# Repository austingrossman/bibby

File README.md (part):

# bibby — Brew In A Bag Temperature Ramp Controller

`bibby` is a temperature and power controller for electric brew-in-a-bag (BIAB)
brewing, running on a Raspberry Pi 5. It reads kettle temperature from a PT100
RTD, drives two mains heating elements through solid-state relays (SSRs), and
presents a touch UI for setting and tracking the brew temperature. Power is
delivered as a duty cycle synchronized to the AC mains zero crossing, and the
whole system is built so that any fault, crash, or hang leaves the heaters
**off**.

This README is meant to let someone unfamiliar with the project understand it,
reproduce the hardware, build the software, and calibrate it for their own
kettle. It moves from the big picture down to the details: architecture, then
hardware, then software, then build/bring-up, then calibration.

This project is for fun. I am doing it to improve my home brewing set up. I hope
that someone sees inspiration in this project and does something similar. I am
doing this with a couple specific goals in mind:
- Learn to use AI for coding purposes.
- I recently purchased a Mac mini. I will only use a Mac for this project and it
  forces me to learn how to use it.
- I've recently acquired a 3D printer. This project has one 3D printed part, so
  I should learn how to use it.

---

## Table of contents

1. [System overview](#1-system-overview)
2. [Software architecture](#2-software-architecture)
3. [Safety design](#3-safety-design)
4. [Hardware](#4-hardware)
5. [Raspberry Pi bring-up and installation](#5-raspberry-pi-bring-up-and-installation)
6. [Building bibby](#6-building-bibby)
7. [Configuration](#7-configuration)
8. [Running](#8-running)
   - [Web interface — screen mirror + log browser](#web-interface)
9. [Calibration methodology](#9-calibration-methodology)
10. [Data logging](#10-data-logging)
11. [Repository layout](#11-repository-layout)
12. [License](#12-license)

---

## 1. System overview

The controller is a **single process** with three threads sharing one in-memory
state block of C11 atomics (the optional web interface adds a few more, none of
them on the control path — §2.9):

```
  +----------------------------------------------------------------+
  |                    bibby (one process)                          |
  |                                                                |
  |  main/UI thread          sampler thread         SSR thread     |
  |  ---------------         ------------------     -------------  |
  |  LVGL touch UI on        60 Hz, DRDY-paced:     SCHED_FIFO,    |
  |  /dev/fb0 (rotated)      - MAX31865 read        ZC-paced:      |
  |  - kettle readout        - temp filter          - zero-cross   |
  |  - charts, slider        - PID (watts)            capture      |
  |  - fault band            - power split          - sigma-delta  |
  |          |               - CSV logging            SSR firing   |
  |          |               - batch-size estimator - watchdogs    |
  |          v                     |                     |         |
  |  +------------------ BibbyState (C11 atomics) -------+         |
  |            duties, temps, modes, faults, history               |
  +----------------------------------------------------------------+
        | SPI0 + DRDY (GPIO16)      | GPIO20 ZC     | GPIO21/26
        v                           |               v
  +-------------+            +-------------+   +-----------+
  |  MAX31865   |            | zero-cross  |   |   SSR1    |
  |  + PT100    |            | detector    |   |   SSR2    |
  +-------------+            +-------------+   +-----------+
        ^                          ^                |
        | RTD                      | AC mains       | switched mains
     kettle probe                  line sense       to heating elements
```

- The **SSR thread** owns the relays. It runs at real-time priority
  (`SCHED_FIFO`) so a GUI stall can never delay the zero-cross response or the
  watchdogs.
- The **sampler thread** owns the sensor and the control law. It publishes
  per-element duty commands into the shared state; it never touches the relays.
- The **UI thread** is a pure view/controller: it renders the state and writes
  user intent (setpoint, mode, manual watts). Nothing in it is on the control
  or safety path.
- Optionally, the **web interface** (§2.9) adds an accept thread, a
  framebuffer-capture thread and a short-lived thread per HTTP connection. They
  run at normal priority, hold no control state of their own, and reach the
  controller only by injecting pointer events into the UI — so everything above
  is unchanged whether it is running or not.

### Why a duty cycle synchronized to zero crossing?

The heating elements are resistive loads switched by zero-cross SSRs. Switching
only at the AC zero crossing eliminates the inrush/EMI of phase-angle control.
Power is modulated by choosing *which* mains half-cycles to pass — a duty cycle
in `[0, 1]`. A sigma-delta modulator (§2.3) spreads the fired cycles out evenly
so the average power tracks the command with minimal low-frequency flicker.

### Why watts, not duty?

The control law works in **watts**: the PID outputs a total power demand, and a
splitter turns watts into per-element duties using the configured element
ratings. This makes the tuned gains independent of which elements are fitted —
swap elements, update `bibby.ini`, and the loop still commands the same power
per degree of error. It also enables the equal-flux split and anti-scorch cap
(§2.4), which need to know real watts per cm².

---

## 2. Software architecture

### 2.1 Shared state — `src/state.{h,c}`

`BibbyState` is a single struct of C11 atomics shared by the three threads —
no locks on the hot paths. Key fields:

| Field | Writer | Purpose |
|---|---|---|
| `duty1`, `duty2` | sampler | per-element duty commands in `[0,1]` |
| `p_demand_w` | sampler | commanded power — also the delivered average power (§2.3) |
| `temp_raw_c`, `temp_filt_c`, `temp_valid` | sampler | latest sensor sample and validity |
| `setpoint_c`, `manual_mode`, `manual_power_w`, `grain_in` | UI | user intent |
| `simulate_zc` | main, at startup | bench zero-cross simulation (`mains.simulate_zc` / `--sim-zc`); never changes while running |
| `output1`, `output2`, `zc_count`, `watchdog_alarm` | SSR thread | fired state, ZC counter, ZC watchdog |
| `control_heartbeat` | sampler | bumped every loop pass; the SSR thread's staleness watchdog watches it |
| `rtd_fault`, `rtd_unresponsive`, `fault_forced_manual` | sampler | sensor-fault state |
| `m_est_l`, `adaptive_scale` | sampler | batch-size estimate (litres) and gain scale |
| `running` | main | global shutdown flag |

A mutex-guarded ring buffer of `HistPoint`s (one per 0.5 s) feeds the UI
charts; it is the only locked structure, and only the UI and the sampler's
0.5 s slow tick touch it.

### 2.2 Sampler thread — `src/sampler_thread.c`

Paced by the MAX31865 DRDY edge (one conversion per mains cycle, so ~60 Hz):

1. **Wait** for a DRDY falling edge (500 ms timeout so a dead sensor cannot
   stall the loop — the read also checks the DRDY level directly, so a missed
   edge still yields the conversion).
2. **Read** the sensor (§2.5); fresh samples go through the temperature filter
   (§2.6) and into the shared state.
3. **Mode interlock:** any RTD fault, unresponsive sensor, or invalid
   temperature forces **manual mode at zero watts** — automatic control can
   never command power on bad data.
4. **Control law** (§2.4): manual watts pass straight through; in auto, the
   watts-based PID runs once per fresh sample.
5. **Power split** (§2.4) turns the demand into `duty1`/`duty2`.
6. **Slow tick (0.5 s):** publish the batch-size estimate (§2.7) and push a
   chart history point.
7. **CSV logging** (§10): one row per fresh sample (or per 0.5 s during an
   outage, so faults stay on disk).

### 2.3 SSR thread — `src/ssr_thread.c`, `src/sigma_delta.h`

Runs at `SCHED_FIFO` (real-time) priority, pinned to the AC zero crossing:

1. **Zero-cross capture.** Wait for a rising edge on GPIO20 (libgpiod v2 edge
   events) with a mains-derived timeout: half-period + 0.7 ms guard — 9.0 ms at
   60 Hz, 10.7 ms at 50 Hz.
2. **Sigma-delta modulation.** Each zero crossing, add each element's duty
   fraction to a per-channel accumulator; fire that SSR for the half-cycle when
   the accumulator reaches 1.0 and subtract 1.0. The accumulator is capped at
   2.0 to bound catch-up after forced-off stretches. This is a first-order
   delta-sigma DAC clocked by the mains: the average fired fraction equals the
   commanded duty with the switching energy pushed to high frequency.
3. **Zero-cross watchdog.** No edge within the timeout → both SSRs forced off,
   `watchdog_alarm` set. A lost mains-sense signal must not leave a relay
   latched on. `simulate_zc` substitutes the timeout tick for the edge so the
   modulator can be exercised with no mains connected. It is set once at
   startup from `mains.simulate_zc` (or `--sim-zc`) and there is deliberately
   **no control for it on the panel**: while it is on this watchdog can never
   trip, which is a commissioning decision, not something a stray tap during a
   brew should be able to do. Startup logs a warning line whenever it is on.
4. **Control-staleness watchdog.** The sampler bumps `control_heartbeat` every
   pass; if it stops advancing for ~2 s worth of zero crossings
   (`2 × mains_Hz`), duties are forced to zero — a wedged control loop must not
   leave the heaters running. (`BIBBY_TEST_WEDGE=<sec>` wedges the sampler once,
   5 s in, to demonstrate exactly this on the bench.)

### 2.4 Control law — `src/control.c`, `src/power_split.c`

**PID (watts).** `p = kp·e`, integrator accumulates raw per-sample error
(`ki` is W/°C per sample), derivative is a raw per-sample delta. Output is
`clamp(ff + p + i + d, 0, max_power)` in watts. Anti-windup is **conditional
integration**: the integrator holds whenever the non-integral output is already
against a rail and the error would push further into it; a backstop clamps the
integral term to full output authority (`max_power / ki`).

**Integral clamp** (`pid.i_clamp_w`, watts; 0 = off). On top of that, the
integral *term* is bounded to ±`i_clamp_w` — the accumulator itself is held to
`i_clamp_w / ki`, every step, whether or not the integrator was allowed to
move. It is a statement of how much authority the integrator may ever have:
with the feedforward carrying the holding power, all the integrator has to
trim is model error, so it never needs kilowatts. The shipped value is 500 W,
about 5 % of the installed 10.5 kW — enough to absorb a wrong ambient or a
drifting `k_loss`, far too little to run away with the kettle. The tighter of
this and the `max_power / ki` backstop wins, and it applies to both gain sets.

**Integral separation** (`pid.i_band_c`, °C; 0 = off). The integrator only
accumulates while `|error| ≤ i_band_c`; outside the band it holds its value,
neither growing nor resetting. Anti-windup alone is not enough on this plant:
the kettle is an integrator, so a PI with an accurate feedforward must finish
a setpoint change with its integrator back near zero, which means every
degree-second of error it soaked up during the approach is paid back as
overshoot after the crossing. In the 2026-09-07 ramp test that accounted for
the whole 0.73 °C overshoot on a 10 °C step: the output was railed (and the
integrator held) only for the first 4 °C, then the integrator wound up for
250 s across the unsaturated approach and was still commanding 1.7 kW over
the holding power when the temperature first touched setpoint. With the
feedforward carrying the holding power the integrator has only model error to
trim, and there is nothing useful for it to learn while the temperature is
still degrees away, so the band confines it to the last half degree. The
band applies to both gain sets.

**Holding feedforward.** `ff = (setpoint − ambient_c) / process_gain_c` watts,
clamped to `[0, max_power]` — the steady-state power needed to hold the
setpoint, supplied directly so the integrator only trims model error (§9.6).
Zero gain disables it.

**Grain-in gain set.** The "Grain In" toggle swaps in an alternate gain set
(`grain.kp/ki/kd`) and optionally caps power (`grain.max_power_w`) — the plant
changes when grain is added, and scorch risk rises. Zero grain gains mean
"same as main gains disabled" (auto commands no power in grain mode until they
are set).

**Adaptive gain scaling** (config-gated, off by default). The batch-size
estimate in litres (§2.7) divided by `adaptive.m_ref_l` scales `kp`/`kd`
within `[scale_min, scale_max]` — a half-size batch gets half the gain without
retuning.

**Equal-flux power split.** Demand is split so both elements run at the same
surface power density (W/cm²): proportional to area, with saturation overflow
pushed to the other element and everything clamped to the element ratings.
With different elements (e.g. 5000 W/820 cm² + 5500 W/473 cm²) the duties are
deliberately unequal — same flux, different power. `power.max_flux_w_cm2`
optionally caps total demand at `flux × total_area` (anti-scorch; 0 disables).

### 2.5 MAX31865 RTD sensor — `src/max31865.c`

- PT100, **3-wire**, 400 Ω nominal reference resistor, on `/dev/spidev0.0` at
  1 MHz, `SPI_MODE_1`.
- **Init sequence:** set 3-wire + clear faults + mains filter notch → enable
  VBIAS (10 ms settle) → enable auto-conversion (20 ms) → discard the first 10
  conversions using DRDY polling (they settle after VBIAS/auto enable).
- **Mains filter:** config-register bit 0 selects the noise-rejection notch
  (set = 50 Hz, clear = 60 Hz). It is set from `mains.frequency_hz` (§7) in the
  first config word — before auto-conversion, as the datasheet requires.
- **`max31865_read()` is non-blocking:** it checks the DRDY level (GPIO16,
  active-low); not ready → previous value with `fresh=false`. Otherwise it
  burst-reads RTD + fault registers in one SPI transaction, converts via
  Callendar–Van Dusen, and applies the per-unit `Rref`/gain/offset calibration
  (§9.1–9.2).
- **Fault handling:** the RTD-LSB fault bit and Fault Status register are
  checked every read. A faulted conversion is rejected (the stale value is held
  so the filter is not poisoned) and the latch cleared so the status reflects
  the next conversion. `max31865_fault_text()` decodes the register for the UI
  fault band.

The MAX31865 datasheet is included at [`docs/MAX31865.pdf`](docs/MAX31865.pdf).

### 2.6 Temperature filter — `src/temp_filter.c`

Cascaded boxcar (moving-average) stages — order and window from `bibby.ini`
(default 2 × 40 samples ≈ a second-order CIC with triangular weighting, ~0.65 s
group delay at 60 Hz). The first sample primes every stage so the output starts
at the true temperature instead of ramping from zero.

### 2.7 Batch-size estimator — `src/mass_estimator.c`

During any stretch of roughly constant commanded power (taken as 0 W while the
ZC watchdog holds the SSRs off) where the temperature rises ≥ 1 °C, the kettle behaves as an integrator: `dT/dt = P/(m·c)`. A
least-squares slope over the stretch gives the thermal mass `P/slope` in J/°C,
which is reported as the equivalent litres of water, `m = (P/slope)/4186`, so
the number on the status line (`m 53.2 L`) and in the log (`m_est_l`) is a
batch size a brewer can sanity-check against what they poured in. It reads a
little high because the kettle, elements and hoses count as water, and it
reads `1/s` high when the elements put out a fraction `s` of their rated watts
(the shipped setup reads 53 L for 45 L poured; §9.4). It is always computed
and logged; feeding it back into the gains is the separate, config-gated
adaptive scaling of §2.4.

### 2.8 UI — `src/ui/`

LVGL 9.3 rendering directly to the framebuffer:

- **Display:** `lv_linux_fbdev` on `/dev/fb0`; the physical panel is portrait,
  mounted sideways, so the UI renders 1280×720 and LVGL software-rotates 90°
  into the 720×1280 framebuffer (`ui.rotation`). Touch comes from the first
  evdev device advertising absolute multitouch (`ui.touch_device = auto`).
- **Layout:** two large square toggles (Grain In, Manual Control) and the
  ±10/±1/±0.1 setpoint steppers on top; temperature chart (setpoint, filtered,
  raw, grain and mode-change markers) and power/PID-term chart below, each
  between a row of tappable legend chips above and a time scale below; a wide
  vertical power slider (manual watts in manual, live demand readout in auto);
  kettle graphic whose element glow follows the commanded duties and whose
  contents carry the batch-size estimate in litres and gallons, with the
  per-element duties and the adaptive gain scale under it; fault band (decoded
  RTD faults, watchdog, forced-manual notice).
- **Time scale:** both charts are right-aligned to *now* and span
  `ui.chart_window_min`, so the scale is fixed at startup and drawn once —
  six marks running `-5m … -1m … now` for the default 5-minute window, landing
  exactly on the chart's vertical grid lines (sub-minute marks read `-0:30`).
- **No dead space.** The two panes stretch from just under the toggles to the
  bottom edge. The fault band has no reserved strip: it is hidden nearly
  always, so it floats over the lower third of the power chart when it
  appears, which costs nothing — the loop is at zero watts by then.
- **Sized for fingers, not a mouse.** Every target is a touch target: the two
  toggles are 180×160, the steppers 120×75, the legend chips 46 px tall, and
  the power slider is 104 px wide — it is the only continuous control on the
  screen, so it gets a thumb's worth of track. The one thing the panel
  deliberately cannot do is arm zero-cross simulation (§2.3).
- LVGL is pinned to **v9.3.0**: v9.4 breaks the fbdev software-rotation path
  and hangs in `lv_deinit` on shutdown.
- **Memory (`src/ui/lv_conf.h`):** LVGL's built-in allocator is a fixed pool
  sized for microcontrollers — 64 KB by default, and this screen sits at ~36 KB
  of it with peaks near 42 KB, so a large redraw could exhaust the remainder and
  assert inside `lv_draw_add_task` ("Out of memory"). bibby therefore sets
  `LV_USE_STDLIB_MALLOC = LV_STDLIB_CLIB`: LVGL allocates from the system heap
  and there is no ceiling to tune.
- **Assertions:** LVGL's default `LV_ASSERT_HANDLER` is `while(1);`, which would
  wedge the UI thread at 100 % CPU — panel frozen, SIGTERM ignored, control
  threads still driving the elements. bibby sets it to `abort()` instead: the
  process dies, the kernel drops the GPIO requests, the SoC pull-downs hold the
  SSR inputs low, and `bibby.service` restarts it (§5.3).
- The kernel console shares `/dev/fb0` and will draw its blinking cursor over
  the UI; the systemd unit unbinds it (§5.3).

`bibby --ui-test` shows a bring-up screen instead: border, corner labels, and a
crosshair that follows the finger — verifies rotation and touch mapping before
trusting the real UI.

### 2.9 Web interface — `src/web/`

Optional, off by default, and configured entirely from `[web]` in `bibby.ini`
(§7). When enabled it adds an HTTP server on the LAN with two screens: a live
mirror of the touchscreen that can be tapped from a phone or laptop, and a
browser for the CSV run logs. Operator's guide in §8; safety in §3.

```
             browser                       bibby process
   ┌──────────────────────────┐   ┌────────────────────────────────────┐
   │  Screen tab              │   │  accept thread ─┬─ conn thread ─┐  │
   │    long-poll   ─────┼───┼──> /api/screen.png              │  │
   │   pointer events    ─────┼───┼──> /api/input                   │  │
   │                          │   │                                 v  │
   │  Logs tab                │   │        capture thread     pointer  │
   │   file list, charts ─────┼───┼──> /api/logs /api/log     queue    │
   │   CSV download      ─────┼───┼──> /api/log/download        │      │
   └──────────────────────────┘   │             │               │      │
                                  │        mmap /dev/fb0        │      │
                                  │             │          UI thread   │
                                  │             └──────────> LVGL indev│
                                  └────────────────────────────────────┘
```

- **Screen mirror.** The capture thread `mmap`s `/dev/fb0` read-only and
  compares it against the previous frame; only a genuine pixel change bumps the
  frame sequence. It captures at most `web.screen_fps` times a second, and only
  while a browser is actually asking — an unwatched panel costs nothing.
  Requests **long-poll**: the server holds `/api/screen.png?seq=N` until the
  screen differs from the client's frame `N` (or 10 s pass, answering `204`), so
  a static screen uses no bandwidth and a touch appears within one frame.
  Frames are encoded as PNG (zlib, "Up" filter) — about 50 KB for a full
  1280×720 frame, and `?scale=2` halves each dimension for slow links.
- **Un-rotation.** The framebuffer is the *physical* portrait panel, sideways;
  the mirror applies `ui.rotation` so the browser shows what the operator at the
  kettle sees. The forward map is the same one LVGL uses on pointer input, so
  "display space" here is exactly LVGL's logical screen.
- **Pointer injection.** Taps post to `/api/input` in display coordinates. The
  server maps them back to panel coordinates and pushes them onto a small queue;
  a **second LVGL pointer indev**, created on the UI thread, drains that queue
  and reports the samples exactly as the evdev touchscreen does — so LVGL
  applies the same rotation to a remote tap as to a finger, and it lands on the
  pixel it looks like it lands on. LVGL is single-threaded and this queue is the
  entire boundary: no web thread ever makes an `lv_*` call. A press with no
  follow-up is auto-released after 2 s, so a browser that vanishes mid-drag
  cannot leave a widget held down.
- **Log browser.** `/api/logs` walks the CSV tree; `/api/log` streams one file
  through a bounded-memory decimator (rows accumulate into buckets; when the
  bucket array fills, adjacent buckets merge pairwise and the rows-per-bucket
  doubles) and returns a whole-file average of at most ~1400 points per series.
  A 75 MB, 459 k-row tuning log becomes 136 KB of JSON in about a second.
  `/api/log/download` serves the raw CSV, including the run in progress.
- **Path safety.** Every client-supplied path is `realpath()`d and required to
  resolve inside `~/bibby/logs` and to be a regular `.csv` file, so the server
  cannot be talked into serving anything else.
- **Authentication.** HTTP Basic against `web.user` / `web.password`, compared
  length-independently so a wrong password cannot be narrowed down by timing.
  The server **refuses to start with an empty password**. Failures are logged
  and answered after a 300 ms delay.
- **Cost.** Nothing at all when no browser is watching — the capture thread
  sleeps on a condition variable. With one browser on the Screen tab, measured
  on a Pi 5 at 1280×720 (percentages are of **one** core, of four; bibby idles
  at ~1.4 %):

  | | per frame | 2 fps | 5 fps |
  |---|---|---|---|
  | full resolution | ~19 ms, ~48 KB | ~5 % | ~11 % |
  | `scale=2` | ~8 ms, ~25 KB | ~3 % | ~6 % |

  The cost is linear in `web.screen_fps`, and the dominant term is the
  **un-rotate/pixel conversion (~8 ms), not the PNG compression (~11 ms
  including the filter)** — rotating means walking the framebuffer down a
  column, which defeats the cache. Two things keep it in hand: the conversion
  precomputes a per-pixel and per-row byte step instead of transforming each
  pixel's coordinates (worth ~10×), and the build is optimized (§6 — an
  unoptimized build costs ~67 ms per frame instead of 19). The web threads run
  at normal priority and are not on the control path; the SSR thread's
  `SCHED_FIFO` and the staleness watchdog are unaffected either way.
- The page is a single self-contained HTML file (`src/web/www/index.html`, no
  external assets or CDN) compiled into the binary at build time, so an
  installed `bibby` has no companion asset directory to lose.

---

## 3. Safety design

This system switches mains voltage into multi-kilowatt heating elements, so the
**default state is always off**. The design requirements and how they are met:

| Requirement | Mechanism |
|---|---|
| Heaters off at startup | SSR GPIO lines are requested with output value low before any thread runs |
| Heaters off on exit/crash | the kernel releases the GPIO lines when the process dies — for any reason — and the SoC pull-downs hold the SSR inputs low; SIGINT/SIGTERM additionally shut down in order |
| Only one instance | `flock` single-instance guard (`src/single_instance.h`); the kernel drops the lock on any exit |
| Heaters off if mains-sense (ZC) is lost | mains-derived zero-cross watchdog (~9 ms at 60 Hz) forces SSRs off, raises `watchdog_alarm`. The one thing that defeats it is bench mode (`mains.simulate_zc`, §2.3), which is why it lives in the config file and has no control on the panel |
| Heaters off if the control loop wedges | control-staleness watchdog: sampler heartbeat stalled for ~2 s of ZCs → duties forced to zero |
| GUI stalls cannot delay safety logic | the SSR thread runs `SCHED_FIFO`; the UI is not on the control path |
| No power commanded on unreliable temperature | RTD fault / unresponsive sensor forces manual mode at zero watts; auto is unreachable until the sensor is healthy |
| Power commands always bounded | demand clamped to the configured element ratings (and the optional flux cap) before splitting; duties clamped to `[0,1]` |
| The integrator cannot run away | conditional-integration anti-windup, plus a hard ± bound on the integral term (`pid.i_clamp_w`, 500 W as shipped) and the `max_power / ki` backstop (§2.4) |
| A vanished web client cannot hold a control down | an injected press with no follow-up sample is released after 2 s |
| Controller returns after a crash | `Restart=always` in the systemd unit (§5.3); SSRs are safe during the gap per the kernel-release mechanism above |
| Remote control cannot bypass an interlock | the web interface owns no control logic: it injects pointer events into the same LVGL widgets a finger drives (§2.9), so mode interlocks, clamps and watchdogs apply identically |
| Remote control is off unless deliberately enabled | `[web]` is disabled by default and the server refuses to start without a password; `web.allow_control = false` serves a read-only mirror |

---

## 4. Hardware

### 4.1 Major components

| Item | Notes |
|---|---|
| Raspberry Pi 5 | GPIO chip is `/dev/gpiochip4` on Pi 5 |
| Touchscreen display | 720×1280 DSI panel (Goodix touch), mounted sideways; UI software-rotates 90° |
| PT100 RTD probe | 3-wire, immersed in the kettle |
| 2 × zero-cross SSR | One per heating element; switched by GPIO21 / GPIO26 |
| 2 × resistive heating element | Mains-powered, BIAB kettle (this build: 5000 W and 5500 W) |
| Custom Pi HAT PCB | Sensor front-end + zero-cross detector (§4.2) |

> **TODO (fill in your build):** exact display model, SSR part numbers and
> current rating, fusing/contactor, and mains connector. These are
> deployment-specific and not captured in the repo.

### 4.2 Raspberry Pi HAT PCB — `pi_hat/bibby_pi_hat/`

A KiCad 7+ project (`.kicad_sch`, `.kicad_pcb`, `.kicad_pro`). Open it in KiCad
to view/edit the schematic and board, or to regenerate gerbers
(`pi_hat/bibby_pi_hat/gerbers/`). The HAT carries two functional blocks:

**RTD front-end (U1 — MAX31865):**
- `R1` = 400 Ω 0.1 % — RTD reference resistor (`Rref`). Precision and tempco here
  set the measurement accuracy; this is one of the two per-unit calibration
  anchors (§9.1).
- `C1`, `C3` = 0.1 µF — decoupling / RC filtering.
- SSOP-20 package; SPI to the Pi plus the DRDY data-ready line.

**AC zero-cross detector (U2 — H11AA1 AC-input optocoupler):**
- The H11AA1 has an anti-parallel LED input, so it conducts on both mains
  half-cycles and its phototransistor output pulses around each zero crossing.
- `R3`–`R6` = 43 kΩ, `R2` = 20 kΩ, `R7` = 1 MΩ (! DNI !) — line current-limiting
  and pull/bias network for the optocoupler. The pulse train feeds GPIO20.
- Solder jumpers `JP1`/`JP2`/`JP3` select options on the board.

**Connectors:**
- `J1` — 2×20 stacking header to the Pi GPIO.
- `J2` — Phoenix 1×10 5.08 mm terminal block (field wiring: RTD, mains sense,
  SSR drive).

> The complete, authoritative bill of materials and net list is the KiCad
> schematic itself. The values above are transcribed from it for orientation.

### 4.3 Pin assignments (40-pin header)

| Pin | GPIO | Signal | Direction | Used by |
|---|---|---|---|---|
| 1 | — | 3.3 V | Power | MAX31865 VIN |
| 6 | — | GND | Power | MAX31865 GND |
| 19 | GPIO10 | SPI0 MOSI | Out | MAX31865 SDI |
| 21 | GPIO9 | SPI0 MISO | In | MAX31865 SDO |
| 23 | GPIO11 | SPI0 SCLK | Out | MAX31865 CLK |
| 24 | GPIO8 | SPI0 CE0 | Out | MAX31865 CS |
| 36 | GPIO16 | DRDY | In | MAX31865 DRDY (sampler thread) |
| 37 | GPIO26 | SSR2 | Out | SSR thread |
| 38 | GPIO20 | Zero Cross | In | SSR thread |
| 40 | GPIO21 | SSR1 | Out | SSR thread |

### 4.4 Electrical / wiring overview

```
   MAINS L ---+----------------------------+--------------------+
              |                            |                    |
              |                       [SSR1 load]          [SSR2 load]
              |                            |                    |
        [ZC detector U2]             [Element 1]          [Element 2]
              |  (opto, isolated)          |                    |
              v                       [SSR1 line]          [SSR2 line]
        GPIO20 (ZC in)                     ^                    ^
                                           |                    |
   Pi 3.3V/GPIO control side:        GPIO21 (SSR1)        GPIO26 (SSR2)
                                      drive (3.3V logic into SSR input)

   PT100 RTD --3 wires--> MAX31865 (U1) --SPI0 + DRDY--> Pi
```

- The H11AA1 provides **galvanic isolation** between the mains line-sense and
  the Pi logic.
- The SSRs are driven by 3.3 V GPIO on their input side; their output side
  switches mains into the elements.
- The RTD is a low-voltage measurement isolated from the mains by the kettle
  and the sensor front-end.

> **WARNING:** mains wiring, fusing, grounding/earth bonding, and enclosure
> safety are the integrator's responsibility. Use appropriately rated SSRs and
> heat-sinking, a proper earth connection to the kettle, and a
> contactor/fuse/breaker sized to the elements.

### 4.5 Enclosure

> **TODO (fill in your build):** enclosure material and dimensions, panel cutout
> for the display, ventilation/heat-sinking for the SSRs, and how the Pi + HAT +
> SSRs are mounted. Add photos and mechanical drawings here.

---

## 5. Raspberry Pi bring-up and installation

Tested target: **Raspberry Pi 5**, 64-bit Raspberry Pi OS.

### 5.1 OS and interfaces

1. Flash Raspberry Pi OS (64-bit) and boot the Pi. Install a beefy SD card (or
   other storage) for logging. Find a way to remote-login to the Pi.
2. Enable SPI:
   ```
   sudo raspi-config   # Interface Options -> SPI -> Enable
   ```
   Confirm `/dev/spidev0.0` exists after reboot.
3. The DSI touch display is auto-detected (`display_auto_detect=1` in
   `/boot/firmware/config.txt`). The touch controller registers as a Goodix
   evdev device; bibby finds it automatically.
4. The Pi 5 exposes GPIO via `/dev/gpiochip4`; the code opens it directly. The
   user running bibby needs the `gpio`, `spi`, `video`, and `input` groups (or
   run via the systemd unit, §5.3).

### 5.2 Build dependencies

```
sudo apt update
sudo apt install -y build-essential cmake git libgpiod-dev zlib1g-dev
```

- **libgpiod v2** is required (the code uses the v2 edge-event API). Confirm
  with `gpiodetect` / `pkg-config --modversion libgpiod`.
- **LVGL** is fetched and built from source by CMake (FetchContent) — nothing
  to install. It renders straight to the framebuffer; no X, Wayland, or GL
  stack is needed.
- The analysis tools (§9.4) additionally want
  `pip3 install numpy scipy matplotlib pandas` on whatever machine runs them.

### 5.3 Autostart at boot (systemd)

[`deploy/bibby.service`](deploy/bibby.service) is the reference unit. Besides
starting bibby it handles three things the app cannot do for itself:

- **Unbinds the kernel console from the framebuffer** (`vtcon1`) before start —
  otherwise the console's blinking cursor (and any kernel message) draws over
  the UI — and rebinds it on stop.
- **`LimitMEMLOCK=64M`** so `mlockall(MCL_CURRENT)` succeeds (the default 8 MB
  is too small once LVGL is linked in).
- **`AmbientCapabilities=CAP_SYS_NICE`** so the SSR thread gets its `SCHED_FIFO`
  real-time priority without running the whole process as root.

Install:

```
sudo cp deploy/bibby.service /etc/systemd/system/
sudo systemctl daemon-reload
sudo systemctl enable --now bibby
```

Check status and logs with `systemctl status bibby` / `journalctl -u bibby -f`.
Adjust `User=` and the paths in the unit for your username/checkout. The unit
uses `Restart=always`: the controller comes back if it ever dies, and the SSRs
are safe during the gap (§3).

---

## 6. Building bibby

```
git clone <repo-url> bibby
cd bibby
cmake -S . -B build -DCMAKE_BUILD_TYPE=Release
cmake --build build -j
```

If you omit `CMAKE_BUILD_TYPE`, CMake would normally configure with **no `-O`
flag at all**; `CMakeLists.txt` therefore defaults it to `RelWithDebInfo`
(`-O2 -g`) when it is unset. This matters more than it sounds: an unoptimized
build runs LVGL's renderer and the web mirror's pixel conversion roughly four
times slower (§2.9). Check an existing build tree with

```
grep C_FLAGS build/CMakeFiles/bibby.dir/flags.make
```

and re-run `cmake -S . -B build -DCMAKE_BUILD_TYPE=RelWithDebInfo` if it shows
no `-O2` — a build directory keeps whatever type it was first configured with.

The first configure fetches LVGL (pinned to v9.3.0 — see §2.8) from GitHub.
Two binaries result:

- `build/bibby` — the controller (links `lvgl`, `gpiod`, `z`, `m`, `pthread`,
  `rt`; `z` is only used by the web screen mirror, §2.9)
- `build/tests` — unit tests for the pure modules (no hardware needed):

```
./build/tests
```

`build/` and `logs/` are gitignored. There is no install step yet; run from the
build tree (the systemd unit does the same). The config file is found relative
to the executable (§7), so a copied-out binary works if `bibby.ini` sits next
to it.

---

## 7. Configuration

Runtime parameters that depend on the install (mains region, heating elements,
control gains, calibration) live in **`bibby.ini`**, **not** in the source.
There is no reason to edit a constant in code and rebuild to adapt a new brew
setup.

**Lookup order:** `-c <path>` argument → `$BIBBY_CONFIG` environment variable →
`bibby.ini` next to the executable → `bibby.ini` in the current directory.
A missing file or unknown key falls back to a built-in safe default (60 Hz,
zero gains), so the system still comes up. Comments (`#` or `;`, inline
allowed) and blank lines are ignored.

All keys, with their defaults:

| Key | Default | Effect |
|---|---|---|
| `mains.frequency_hz` | 60 | ZC watchdog timeout (half-period + 0.7 ms), staleness cutoff (2×Hz ZCs ≈ 2 s), MAX31865 notch (50/60 Hz) |
| `mains.simulate_zc` | false | **bench only:** treat ZC-watchdog timeouts as zero crossings, so the whole loop runs with no AC connected (§2.3). The mains-loss watchdog cannot trip while it is on, so it is a config switch with no panel control; `--sim-zc` forces it on for one run |
| `element1.watts` / `element2.watts` | 2500 / 2500 | element ratings; their sum is the maximum power demand |
| `element1.area_cm2` / `element2.area_cm2` | 150 / 150 | wetted areas driving the equal-flux split |
| `power.max_flux_w_cm2` | 0 (off) | anti-scorch cap: total demand ≤ flux × total area |
| `pid.kp` / `ki` / `kd` | 0 | watts-based gains (§9.5); zero = auto commands no power |
| `pid.i_band_c` | 0 (off) | integral-separation band, °C: the integrator only accumulates within it (§2.4); both gain sets |
| `pid.i_clamp_w` | 0 (off) | ± bound on the integral term, watts (§2.4); the tighter of this and the `max_power / ki` backstop applies; both gain sets |
| `grain.kp` / `ki` / `kd` | 0 | alternate gain set while "Grain In" is on |
| `grain.max_power_w` | 0 (off) | power cap while grain is in |
| `feedforward.process_gain_c` | 0 (off) | identified K [°C/W]; holding feedforward `(setpoint−ambient)/K` watts |
| `feedforward.ambient_c` | 20 | feedforward reference temperature |
| `sensor.ref_resistor_ohms` | 400 | MAX31865 Rref, ice-point trimmed (§9.1) |
| `sensor.temp_cal_gain` / `temp_cal_offset` | 1.0 / 0.0 | two-point span trim, `T_true = g·T + b` (§9.2) |
| `filter.order` / `filter.window` | 2 / 40 | boxcar cascade stages and window length (§2.6) |
| `logging.rate` | high | `high` = row per sample (60 Hz); `low` = row per `low_period_s` |
| `logging.low_period_s` | 2.0 | row period in low-rate mode |
| `ui.chart_window_min` | 5 | chart time window, minutes (1–30) |
| `ui.rotation` | 90 | UI rotation onto the panel: 0/90/180/270 |
| `ui.fb_device` / `ui.touch_device` | auto | `auto` = `/dev/fb0` / first multitouch evdev; or explicit paths |
| `web.enable` | false | start the web interface (§8); ignored unless `web.password` is set |
| `web.port` | 8080 | TCP port |
| `web.bind` | 0.0.0.0 | `0.0.0.0` = whole LAN; `127.0.0.1` = the Pi only (ssh tunnel) |
| `web.user` / `web.password` | brewer / *(empty)* | HTTP Basic credentials; **empty password = server refuses to start**. No `#` or `;` (INI comment characters) |
| `web.allow_control` | true | `false` serves a read-only mirror — the screen updates, taps are rejected |
| `web.screen_fps` | 5 | cap on mirror capture rate, 1–30 (only captures while a browser is watching) |
| `adaptive.enable` | false | scale kp/kd by (batch-size estimate / `m_ref_l`) |
| `adaptive.m_ref_l` | 0 | batch size the gains were tuned at, litres, as the estimator reads it (§9.5) |
| `adaptive.scale_min` / `scale_max` | 0.5 / 4.0 | clamp on the adaptive scale |

The shipped `bibby.ini` documents each value's derivation inline; §9 gives the
full procedures.

---

## 8. Running

```
./build/bibby                  # the normal touch UI
./build/bibby --ui-test        # display/touch bring-up screen (§2.8)
./build/bibby --headless       # no display: prints a status line every 2 s
./build/bibby --sim-zc         # start with simulated zero crossings (bench)
./build/bibby --manual-w 8000  # start in manual at 8000 W (plant-ID tests)
./build/bibby -c /path/to.ini  # explicit config
```

If the framebuffer cannot be opened the UI falls back to headless mode rather
than exiting — the controller and safety logic keep running.

### UI elements

- **Kettle card:** setpoint in °C and °F above it, the measured temperature in
  °C and °F at the same size inside it (°F a shade darker, so °C still reads
  first), the batch-size estimate on the contents in **litres and US gallons**,
  animated elements whose glow tracks the commanded duty, and a per-element
  duty readout below (`E1 x%  E2 y%` — these differ by design; see the
  equal-flux split, §2.4).
- **POWER slider:** commands watts in manual mode; shows the loop's live demand
  in auto (disabled for input). Total watts read out under it. It is 104 px
  wide — deliberately, for a wet thumb.
- **Setpoint steppers:** ±10 / ±1 / ±0.1 °C.
- **Toggles:** two square pads — Grain In (gain set swap + logged event marker)
  and Manual Control (manual watts vs PID auto). Zero-cross simulation is not
  among them; it is `mains.simulate_zc` in the config (§2.3, §7).
- **Charts:** temperature (setpoint / temp / raw + grain-event and mode-event
  markers — short dashes along the top edge at the samples where Grain In or
  Manual flipped) and power (demand W / ff / P / I / D), window set
  by `ui.chart_window_min`, y-autoscaled. Each carries a time scale under it
  reading backwards from `now` to the full window.
- **Chart legends:** each trace has a chip under its chart — tap to drop that
  trace. A hidden trace is neither drawn nor counted in that chart's autoscale,
  so switching off the terms you are not tuning zooms the pane onto the rest.
  Chips are colored when on, greyed and struck through when off; all traces
  start visible on every launch.
- **Fault band:** decoded RTD faults, watchdog alarm, and "Auto disabled →
  manual" when a fault forced the mode switch.
- **Status line:** the adaptive gain scale, under the per-element duties at the
  foot of the kettle column. (The batch-size estimate that drives it is on the
  kettle contents.)

### Web interface

Off by default. To turn it on, set a password in `[web]` (§7) and restart:

```ini
[web]
enable        = true
port          = 8080
bind          = 0.0.0.0        ; 127.0.0.1 to reach it only through an ssh tunnel
user          = brewer
password      = pick-something-long
allow_control = true           ; false for a read-only mirror
screen_fps    = 5              ; halve it if you want the CPU back; 2 is still responsive
```

Then browse to `http://<pi-address>:8080/` and enter the user and password.
Startup logs the URL it is serving and whether control is enabled:

```
web: mirroring /dev/fb0, panel 720x1280 32 bpp, rotation 90 -> 1280x720
web: http://0.0.0.0:8080/ as user "brewer" (remote control ENABLED)
web: remote pointer attached
```

**Screen tab** — a live mirror of the panel, upright the way you see it at the
kettle. It is the real framebuffer, not a re-drawing, so it shows exactly what
the touchscreen shows. Click or drag anywhere on it and the tap is injected
into the UI as a pointer event: setpoint steppers, the power slider, and the
toggles all behave as they do under a finger. Quality can be dropped to half
resolution for a weak connection. The mirror pauses while the Logs tab is open
or the browser tab is hidden.

**Logs tab** — every run under `~/bibby/logs` newest first (the run in progress
is marked "● live"). Pick one to plot it: temperature (filtered / raw /
setpoint) and power (demand, ff/P/I/D, and per-element duty on a
right-hand axis). Legend chips toggle traces, and hovering reads out every
visible series at that instant. **Download CSV** fetches the raw file — the
same one `tools/identify_plant.py` and `tools/plot_logs.py` expect — so a brew
can be pulled off the Pi from a laptop without ssh. Long logs are averaged
server-side to about 1400 points for plotting; the download is always the full,
unmodified file.

**Before you enable it, read this.** The mirror puts the kettle controls on
your network. Everything the panel can do, a browser with the password can do,
including raising the setpoint or commanding power on a multi-kilowatt element.
Every interlock still applies — remote taps go through the same widgets, so a
sensor fault still forces manual at 0 W, and the watchdogs are untouched — but
the *authorization* is only that password, over plain HTTP:

- Use it on a trusted home network, with a password you use nowhere else.
- **Do not forward the port through your router.** There is no TLS; anyone who
  can watch the traffic can read the password. For access from outside the
  house, set `bind = 127.0.0.1` and reach it through an ssh tunnel:
  `ssh -L 8080:localhost:8080 ramp` , then browse to `localhost:8080`.
- Set `allow_control = false` when you only want to watch a brew — the screen
  still updates live, but taps are rejected by the server.
- Leave `enable = false` if you do not want any of this; there is no default
  password and the server will not start without one.

**Bench testing without mains:** set `simulate_zc = true` in `[mains]`, or
start with `--sim-zc` to avoid editing the file. The SSR thread then clocks the
sigma-delta from its timeout tick instead of the missing zero-cross edge; the
full UI, control law, and logging run with no AC connected. Startup prints

```
bibby: ZERO-CROSS SIMULATION ON (--sim-zc) - the mains-loss watchdog cannot trip; bench use only
```

**Turn it off before the controller is wired to a kettle.** With it on, losing
the mains-sense signal looks exactly like normal operation to the SSR thread,
so the ZC watchdog — one of the interlocks in §3 — is inert. There
is no toggle for it on the panel for that reason: it should change when the
unit is on a bench, not when someone is brewing on it.

---

## 9. Calibration methodology

Three of the measurement constants are **per-unit** — they depend on the
specific RTD probe and the board's reference resistor, so they **must be
re-derived for any other board or probe**. All three live in the `[sensor]`
section of `bibby.ini`; **none require a code change or rebuild**. Their
identity defaults (`Rref` = 400 Ω, gain = 1.0, offset = 0.0) give a working but
uncalibrated sensor.

`tools/calibrate_sensor.py` does the §9.1/§9.2 arithmetic for you (standard
library only):

```
python3 tools/calibrate_sensor.py rref --ice-reading 1.4 --rref-current 400
python3 tools/calibrate_sensor.py span --p1 0.0 0.0 --p2 25.0 23.78
```

| `bibby.ini` key | Symbol | What it corrects |
|---|---|---|
| `sensor.ref_resistor_ohms` | `Rref` | one-point offset at the ice point (§9.1) |
| `sensor.temp_cal_gain` | `g` | span/slope error across temperature (§9.2) |
| `sensor.temp_cal_offset` | `b` | residual offset after the span fit (§9.2) |

The driver applies them in this order, so **calibrate in this order too**:

```
R_rtd  = (raw / 32768) * Rref            # ref_resistor_ohms  (§9.1)
T_cvd  = CVD(R_rtd)                      # Callendar–Van Dusen, fixed
T_true = g * T_cvd + b                   # gain, offset       (§9.2)
```

### 9.1 Reference resistor `Rref` (ice-point one-point trim)

`Rref` scales the entire resistance reading, so trimming it nulls a constant
offset. Trim it first, at a single known low temperature (the ice point is the
cheapest 0 °C reference available).

**Procedure**

1. Set `sensor.temp_cal_gain = 1.0`, `sensor.temp_cal_offset = 0.0` (so the
   span trim does not mask the reading), and `sensor.ref_resistor_ohms` to the
   board's nominal reference (400 Ω here — the value of `R1` on the HAT, §4.2).
2. Submerge the probe in a well-stirred ice-water bath and let it settle.
3. Read the measured temperature `T_ice` (the **raw** column in the CSV log,
   §10, before any span trim).
4. The PT100 resistance the probe *should* present at `T_ice` is, from
   Callendar–Van Dusen with `R0 = 100 Ω`, `A = 3.9083e-3`:
   `R_pt100(T) = 100·(1 + A·T + B·T²)`, which near 0 °C is ≈ `100·(1 + A·T)`.
   Because the reading scales linearly with `Rref`, the trimmed value is:

   ```
   Rref = Rref_nominal · 100.0 / R_pt100(T_ice)
   ```

**Worked example (this unit):** read **+1.4 °C** in the ice bath.
`R_pt100(1.4) = 100·(1 + 3.9083e-3·1.4) ≈ 100.547 Ω`, so
`Rref = 400 · 100.0 / 100.547 = 397.82 Ω` → `sensor.ref_resistor_ohms = 397.82`.

### 9.2 Span trim `gain`/`offset` (two-point line fit)

With `Rref` set, a probe can still read low or high **in proportion to
temperature** (a probe α / self-heating mismatch). That is a slope error, so it
is corrected in the temperature domain by a straight line through **two**
reference points `(T1_ref, T1_meas)` and `(T2_ref, T2_meas)`, where `T_meas` is
the reading **after** the §9.1 trim:

```
gain   = (T2_ref - T1_ref) / (T2_meas - T1_meas)
offset =  T1_ref - gain · T1_meas
```

Pick the two points as far apart as practical and bracketing the brew range for
the best fit. Good choices: the ice point (0 °C) and the local **boiling
point** (altitude-corrected, below). A stirred ambient bath against a trusted
reference thermometer also works for the upper point.

**Boiling-point reference.** Water boils below 100 °C at altitude; approximate
the local boiling point as `T_boil ≈ 100 − 3.4·(h/1000m)` (°C, `h` =
elevation), or read it from a steam table for your barometric pressure, then
use that as the upper `T_ref`.

**Worked example (this unit):** ice point `(0.00, 0.00)` and a fan-mixed
ambient point `(25.00, 23.78)`:
`gain = (25.00 − 0.00)/(23.78 − 0.00) = 1.0513`,
`offset = 0.00 − 1.0513·0.00 = 0.0`. After a small refinement the shipped
values are `sensor.temp_cal_gain = 1.0528`, `sensor.temp_cal_offset = -0.032`.

> **PROVISIONAL:** both points above are ≤ 25 °C. Re-fit using a boiling-point
> upper reference before trusting brew-range temperatures — at 5230 ft the
> local boiling point is **94.7 °C**, and the §9.1-trimmed RTD should read
> ~90.0 °C there. Re-derive both keys for your own probe and altitude.

### 9.3 Process model

The model of the signal chain from power command to measured temperature has
three cascaded stages: the kettle thermal plant, the RTD probe lag, and the
software filter.

#### Signal chain

```
  P [W] ──►[ G_plant ]──► T_kettle ──►[ G_probe ]──►[ G_filt ]──► T_meas ──► PID
            K/(τs+1)                  1/(τ_pr s+1)   boxcar cascade

  plant heat loss: T_kettle relaxes toward ambient at rate k_loss·(T − T_amb)
```

#### Kettle thermal plant

Energy balance of a well-stirred (recirculated) kettle, linearised about an
operating point: the stored energy rises with the electrical power poured in
and falls with the heat leaking to the room.

$$m\,c_p\,\frac{dT}{dt} \;=\; P \;-\; k_{\text{loss}}\,\bigl(T - T_{\text{amb}}\bigr)$$

| Symbol | Meaning | Units |
|---|---|---|
| $T$ | kettle liquid temperature — the controlled variable | °C |
| $T_{\text{amb}}$ | ambient temperature the kettle relaxes toward unpowered | °C |
| $P$ | total electrical power delivered by the elements — the manipulated variable | W |
| $m$ | liquid mass | kg |
| $c_p$ | specific heat, 4186 for water | J/(kg·°C) |
| $k_{\text{loss}}$ | total heat-loss coefficient (conduction through walls and lid, radiation, evaporation) | W/°C |

Work in deviation variables so the constant ambient term drops out. Let
$\theta \equiv T - T_{\text{amb}}$; with $T_{\text{amb}}$ constant
$\dot\theta = \dot T$, so

$$m\,c_p\,\dot\theta + k_{\text{loss}}\,\theta \;=\; P$$

Laplace transform, starting from the operating point so $\theta(0) = 0$:

$$m\,c_p\,s\,\Theta(s) + k_{\text{loss}}\,\Theta(s) \;=\; P(s)
\quad\Longrightarrow\quad
\bigl(m\,c_p\,s + k_{\text{loss}}\bigr)\,\Theta(s) \;=\; P(s)$$

Solve for the transfer function and divide numerator and denominator by
$k_{\text{loss}}$ to reach standard first-order form:

$$G_{\text{plant}}(s) \;=\; \frac{\Theta(s)}{P(s)}
\;=\; \frac{1}{m\,c_p\,s + k_{\text{loss}}}
\;=\; \frac{1/k_{\text{loss}}}{\dfrac{m\,c_p}{k_{\text{loss}}}\,s + 1}
\;=\; \frac{K}{\tau s + 1}$$

$$K = \frac{1}{k_{\text{loss}}}\ \left[\text{°C/W}\right]
\qquad
\tau = \frac{m\,c_p}{k_{\text{loss}}}\ \left[\text{s}\right]$$

where $K$ is the steady-state gain (°C of rise per watt held) and $\tau$ the
dominant time constant.

For a 30 L batch in a reasonably insulated kettle $\tau$ is typically **20–40
minutes**. The initial ramp rate at power $P$ is $P/(m\,c_p)$ — easy to check
directly against the heating phase of the identification test, and the basis of the online $m\,c$ estimator
(§2.7).

#### RTD probe lag

The PT100 element sits inside a sheath with its own thermal mass, so it reports
a lagged version of the liquid temperature. Treating the sheath as a lumped
mass exchanging heat with the liquid through a film conductance gives the same
first-order form as the kettle:

$$m_{\text{pr}}\,c_{\text{pr}}\,\frac{dT_{\text{pr}}}{dt}
\;=\; h A\,\bigl(T - T_{\text{pr}}\bigr)
\quad\Longrightarrow\quad
\tau_{\text{probe}}\,\dot T_{\text{pr}} + T_{\text{pr}} \;=\; T$$

$$G_{\text{probe}}(s) \;=\; \frac{T_{\text{pr}}(s)}{T(s)}
\;=\; \frac{1}{\tau_{\text{probe}}\,s + 1},
\qquad \tau_{\text{probe}} = \frac{m_{\text{pr}}\,c_{\text{pr}}}{hA}
\;\approx\; 5\text{–}30\ \text{s}$$

| Symbol | Meaning | Units |
|---|---|---|
| $T_{\text{pr}}$ | temperature the probe actually reports | °C |
| $T$ | true liquid temperature (the plant output above) | °C |
| $m_{\text{pr}} c_{\text{pr}}$ | thermal mass of the sheath and element | J/°C |
| $hA$ | film conductance from liquid to sheath | W/°C |
| $\tau_{\text{probe}}$ | probe time constant — thin bare sheath at the low end, thick thermowell at the high end | s |

Its DC gain is 1: the probe eventually reaches the liquid temperature, it just
gets there late. That is why $\tau_{\text{probe}}$ shows up as dead time in the
FOPDT fit rather than as a gain error.

#### Software filter

The default filter is $n = 2$ cascaded boxcars of $N = 40$ samples each, run at
the sensor rate $f_s \approx 60\ \text{Hz}$ (one conversion per mains cycle).
A single $N$-sample boxcar is

$$G_{\text{box}}(z) \;=\; \frac{1}{N}\sum_{k=0}^{N-1} z^{-k},
\qquad
G_{\text{filt}}(z) \;=\; \bigl[G_{\text{box}}(z)\bigr]^{\,n}$$

Its taps are uniform, so the group delay is the mean tap index — $(N-1)/2$
samples — and $n$ identical stages in series simply add:

$$L_{\text{filt}}
\;=\; \frac{n\,(N-1)}{2\,f_s}
\;=\; \frac{2 \cdot 39}{2 \cdot 60}
\;\approx\; 0.65\ \text{s}$$

with each stage contributing $(N-1)/(2 f_s) \approx 0.33\ \text{s}$. Both $n$
and $N$ are `filter.order` / `filter.window` in the INI; changing them changes
the dead time below, so re-identify the plant afterward.

#### Combined FOPDT approximation

Cascading the three stages gives a third-order model. The two small lags —
probe and filter — are far faster than the kettle, so the standard reduction
(Skogestad half-rule, in the limit where the small time constants are much
smaller than the dominant one) folds them into a pure delay:

$$G(s) \;=\; \underbrace{\frac{K}{\tau s + 1}}_{\text{kettle}}
\cdot \underbrace{\frac{1}{\tau_{\text{probe}} s + 1}}_{\text{probe}}
\cdot \underbrace{G_{\text{filt}}(s)}_{\text{filter}}
\;\;\approx\;\; \frac{K\,e^{-Ls}}{\tau s + 1}$$

using $\dfrac{1}{\tau_{\text{probe}} s + 1} \approx e^{-\tau_{\text{probe}} s}$
for $\tau_{\text{probe}} \ll \tau$, so the delays add:

$$K \approx \frac{1}{k_{\text{loss}}}\ \left[\text{°C/W}\right]
\qquad
\tau \approx \frac{m\,c_p}{k_{\text{loss}}}\ \left[\text{s}\right]
\qquad
L \approx \tau_{\text{probe}} + L_{\text{filt}}\ \left[\text{s}\right]$$

The ratio $L/\tau$ characterises controllability: $L/\tau < 0.3$ is
straightforward; $L/\tau > 1.0$ is delay-dominated. A BIAB kettle sits well
below 0.3 — with $L \approx 10\text{–}30\ \text{s}$ against a $\tau$ of tens of
minutes, the challenge is the large time constant, not the dead time.

#### Gain conventions — continuous vs. INI

The PID accumulates raw error once per sample (`integral += e`, not `e·dt`)
and uses raw per-sample deltas for the derivative. The INI gains relate to
continuous-time gains by:

```
kp_ini = Kp_c            [W/°C, unchanged]
ki_ini = Ki_c · T_s      [T_s = sample period ≈ 1/60 s]
kd_ini = Kd_c / T_s
```

`identify_plant.py` measures `T_s` from the log and folds it in automatically.

### 9.4 System identification

`m` (the batch size, litres), `k_loss`, and `L` come from a **heat-then-cool test**: run the elements
at a fixed high power in manual mode until the kettle reaches mash
temperature, then turn them off and let it cool. `tools/identify_plant.py`
drives the lumped model of §9.3 with the logged power demand `p_demand_w`
(which the modulator delivers, §2.3; rows where the ZC watchdog was up count
as 0 W), fits the three parameters to the measured temperature by least
squares, and prints ready-to-paste `[pid]`/`[feedforward]` blocks.

Each phase pins down something the other cannot:

| Phase | Determines | Why |
|---|---|---|
| Heating ramp | `m` | slope = P / (m·c); the loss term is small against 8 kW |
| Power on/off corners | `L` | the measured trace turns `L` seconds after the power does |
| Cooling decay | `k_loss` | at 0 W the kettle relaxes toward ambient at rate k_loss / m·c |

A constant-power step alone cannot separate `K` from `τ` unless it runs to
steady state, which for a BIAB kettle at any useful power sits above boiling.
The cooling phase removes that problem: `K = 1/k_loss` and `τ = m·c/k_loss`
follow directly.

#### Test procedure

1. **Fill** the kettle to the intended brew volume, with the lid and the
   recirculation pump exactly as you will brew. `k_loss` depends on the lid,
   insulation, and pump heat, so the test setup must match the brew setup.
   Good mixing is required for the lumped model to hold.
2. **Measure the room temperature** with a separate thermometer near the
   kettle. This is the `--ambient` input; the script does not estimate it.
3. **Start bibby** (the CSV logger runs from startup) and leave it a minute at
   0 W so the log has a quiet lead-in.
4. **Heat.** Manual Control on; set the power slider to about **80 %** of
   maximum and leave it until the temperature reaches mash temperature
   (**~65 °C**). Do not approach boiling: evaporation changes `k_loss`.
   (`--manual-w` on the command line applies the power from startup.)
5. **Cool.** Slider to 0 W. Leave the pump running and the lid as it was, and
   let the kettle cool until the temperature has dropped **at least 5 °C**;
   30 minutes or more is better. The longer the decay, the tighter `k_loss`.
   A well-insulated kettle cools very slowly (a cooling time constant of
   hours is normal), so give it an hour or more — the holding power near mash
   temperature is pinned down early, but separating `k_loss` from the ambient
   value takes a longer decay.
6. **Stop** bibby and copy the log from `~/bibby/logs/YYYY/MM/DD/HH-MM-SS.csv`.

The power trace does not have to be clean — the script uses whatever
`p_demand_w` was, sample by sample — but the plant must not
change mid-test (no adding water, no lid on/off).

#### Running the identification

```
pip3 install numpy scipy matplotlib pandas    # once

python3 tools/identify_plant.py logs/YYYY/MM/DD/HH-MM-SS.csv \
        --ambient 21.5 --volume-l 45 -o plant_fit.png

# τc (--lambda) sets how aggressive the SIMC gains are (§9.5); the shipped
# bibby.ini uses 30 s, the script's default is max(3L, 120 s):
python3 tools/identify_plant.py logs/... --ambient 21.5 --lambda 30
```

The whole log is used; there is no window to choose. `--ambient` is the room
temperature you measured, in °C; `--volume-l` is the water you put in, used
only for the element-watts cross-check below. The script prints:

- the power phases it found (heat/cool spans, mean watts, temperature range);
- the fitted `m` in litres (compare against what you poured in), `k_loss`, and `L`,
  each with a standard error, the fit RMSE overall and per phase, and a
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
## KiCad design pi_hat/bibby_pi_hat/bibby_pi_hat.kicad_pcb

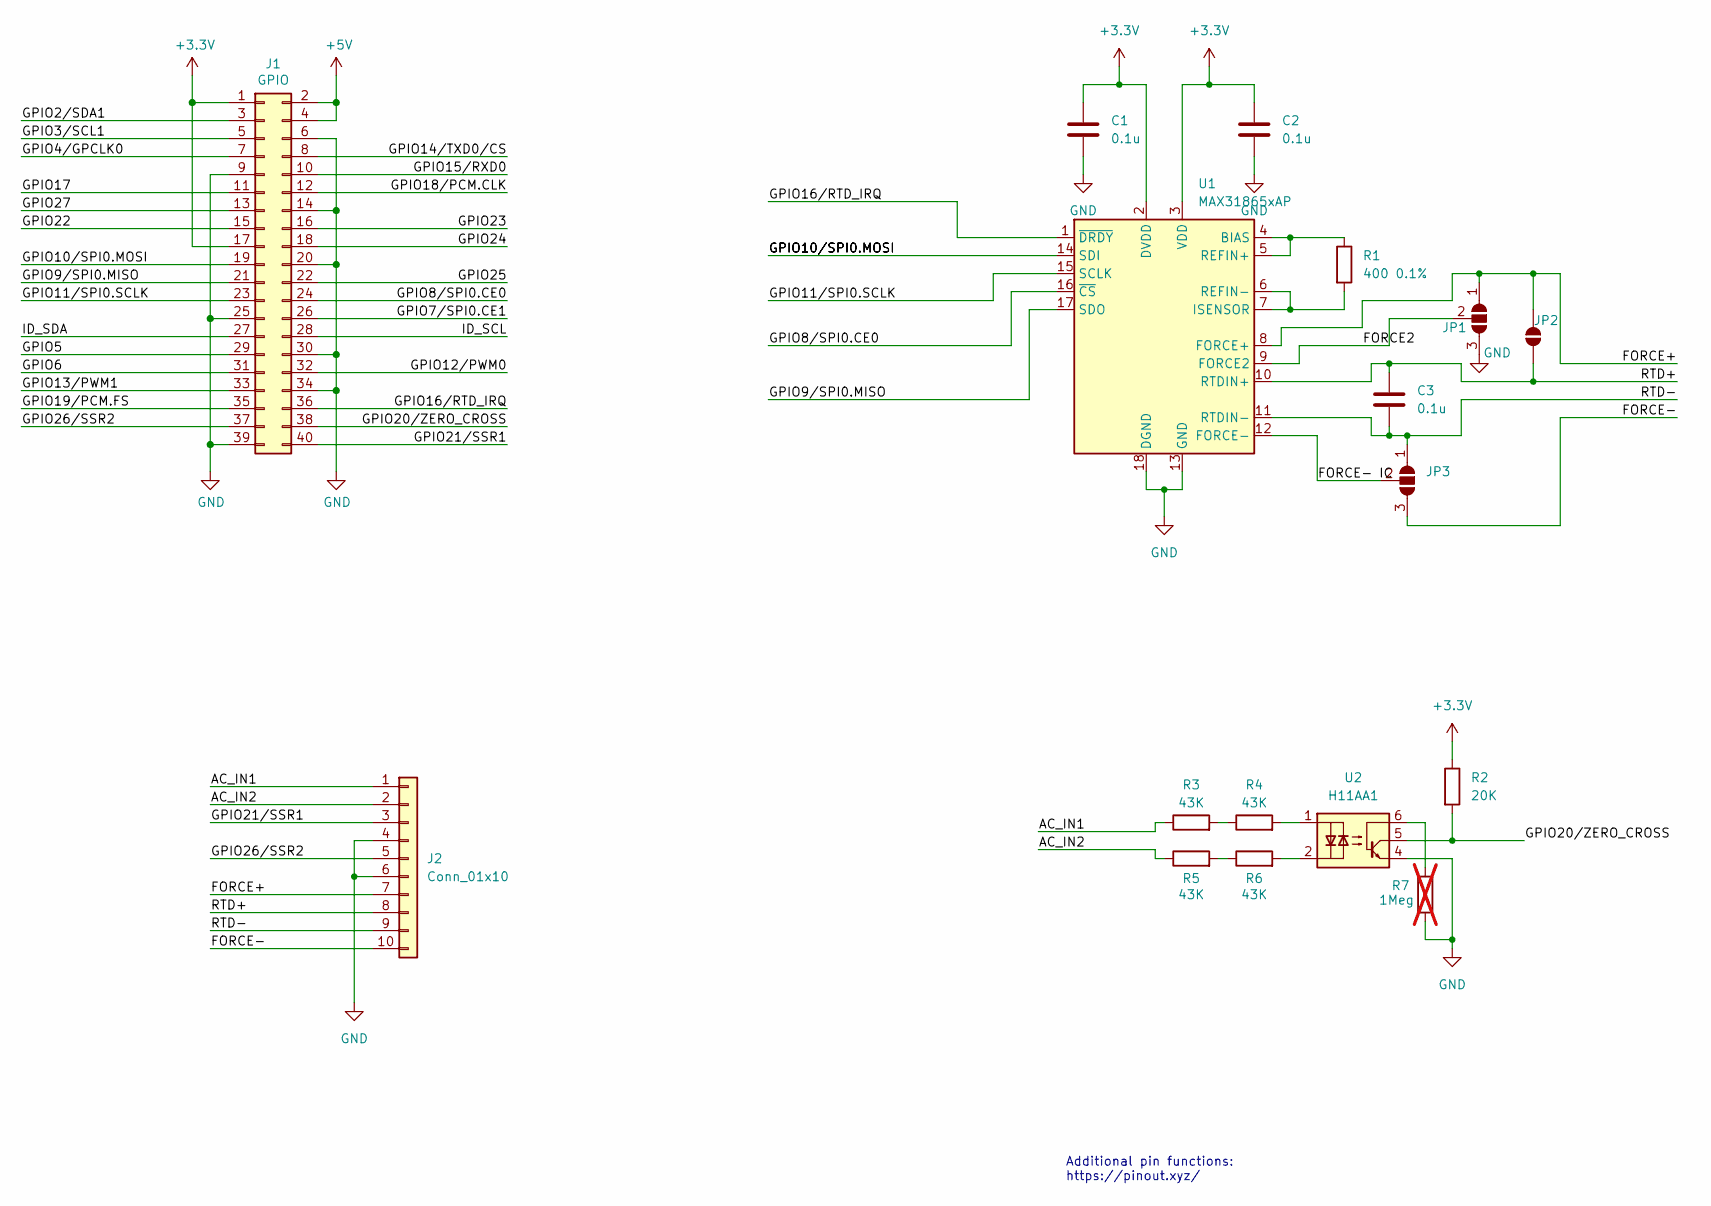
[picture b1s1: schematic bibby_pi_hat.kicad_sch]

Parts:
C1, C2, C3: 0.1u; C_0603_1608Metric_Pad1.08x0.95mm_HandSolder
J1: GPIO; PinSocket_2x20_P2.54mm_Vertical
J2: Conn_01x10; TerminalBlock_Phoenix_MKDS-1,5-10-5.08_1x10_P5.08mm_Horizon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
JP1, JP3: SolderJumper_3_Open; SolderJumper-3_P2.0mm_Open_TrianglePad1.0x1.5mm_NumberLabels
JP2: SolderJumper_2_Open; SolderJumper-2_P1.3mm_Open_TrianglePad1.0x1.5mm
R1: 400 0.1%; R_0603_1608Metric_Pad0.98x0.95mm_HandSolder
R2: 20K; R_0603_1608Metric_Pad0.98x0.95mm_HandSolder
R3, R4, R5, R6: 43K; R_0603_1608Metric_Pad0.98x0.95mm_HandSolder
R7: 1Meg; R_0603_1608Metric_Pad0.98x0.95mm_HandSolder; not fitted
U1: MAX31865xAP; SSOP-20_5.3x7.2mm_P0.65mm
U2: H11AA1; DIP-6_W7.62mm

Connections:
+3.3V: C1.1, C2.1, J1.1, J1.17, R2.1, U1.2 (DVDD), U1.3 (VDD)
+5V: J1.2, J1.4
/AC_IN1: J2.1, R3.1
/AC_IN2: J2.2, R5.1
/FORCE2: JP1.2 (C), U1.9 (FORCE2)
/FORCE+: J2.7, JP1.1 (A), JP2.2 (B), U1.8 (FORCE+)
/FORCE-: J2.10, JP3.3 (B)
/FORCE- IC: JP3.2 (C), U1.12 (FORCE-)
/GPIO2/SDA1: J1.3
/GPIO3/SCL1: J1.5
/GPIO4/GPCLK0: J1.7
/GPIO5: J1.29
/GPIO6: J1.31
/GPIO7/SPI0.CE1: J1.26
/GPIO8/SPI0.CE0: J1.24, U1.16 (~CS)
/GPIO9/SPI0.MISO: J1.21, U1.17 (SDO)
/GPIO10/SPI0.MOSI: J1.19, U1.14 (SDI)
/GPIO11/SPI0.SCLK: J1.23, U1.15 (SCLK)
/GPIO12/PWM0: J1.32
/GPIO13/PWM1: J1.33
/GPIO14/TXD0/CS: J1.8
/GPIO15/RXD0: J1.10
/GPIO16/RTD_IRQ: J1.36, U1.1 (~DRDY)
/GPIO17: J1.11
/GPIO18/PCM.CLK: J1.12
/GPIO19/PCM.FS: J1.35
/GPIO20/ZERO_CROSS: J1.38, R2.2, U2.5
/GPIO21/SSR1: J1.40, J2.3
/GPIO22: J1.15
/GPIO23: J1.16
/GPIO24: J1.18
/GPIO25: J1.22
/GPIO26/SSR2: J1.37, J2.5
/GPIO27: J1.13
/ID_SCL: J1.28
/ID_SDA: J1.27
/RTD+: C3.1, J2.8, JP2.1 (A), U1.10 (RTDIN+)
/RTD-: C3.2, J2.9, JP3.1 (A), U1.11 (RTDIN-)
GND: C1.2, C2.2, J1.6, J1.9, J1.14, J1.20, J1.25, J1.30, J1.34, J1.39, J2.4, J2.6, JP1.3 (B), R7.2, U1.13 (GND), U1.18 (DGND), U1.19 (GND), U2.4
unnamed: R3.2, R4.1
unnamed: R4.2, U2.1
unnamed: R5.2, R6.1
unnamed: R6.2, U2.2
unnamed: R7.1, U2.6
unnamed: R1.1, U1.4 (BIAS), U1.5 (REFIN+)
unnamed: R1.2, U1.6 (REFIN-), U1.7 (ISENSOR)

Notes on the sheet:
Additional pin functions: https://pinout.xyz/

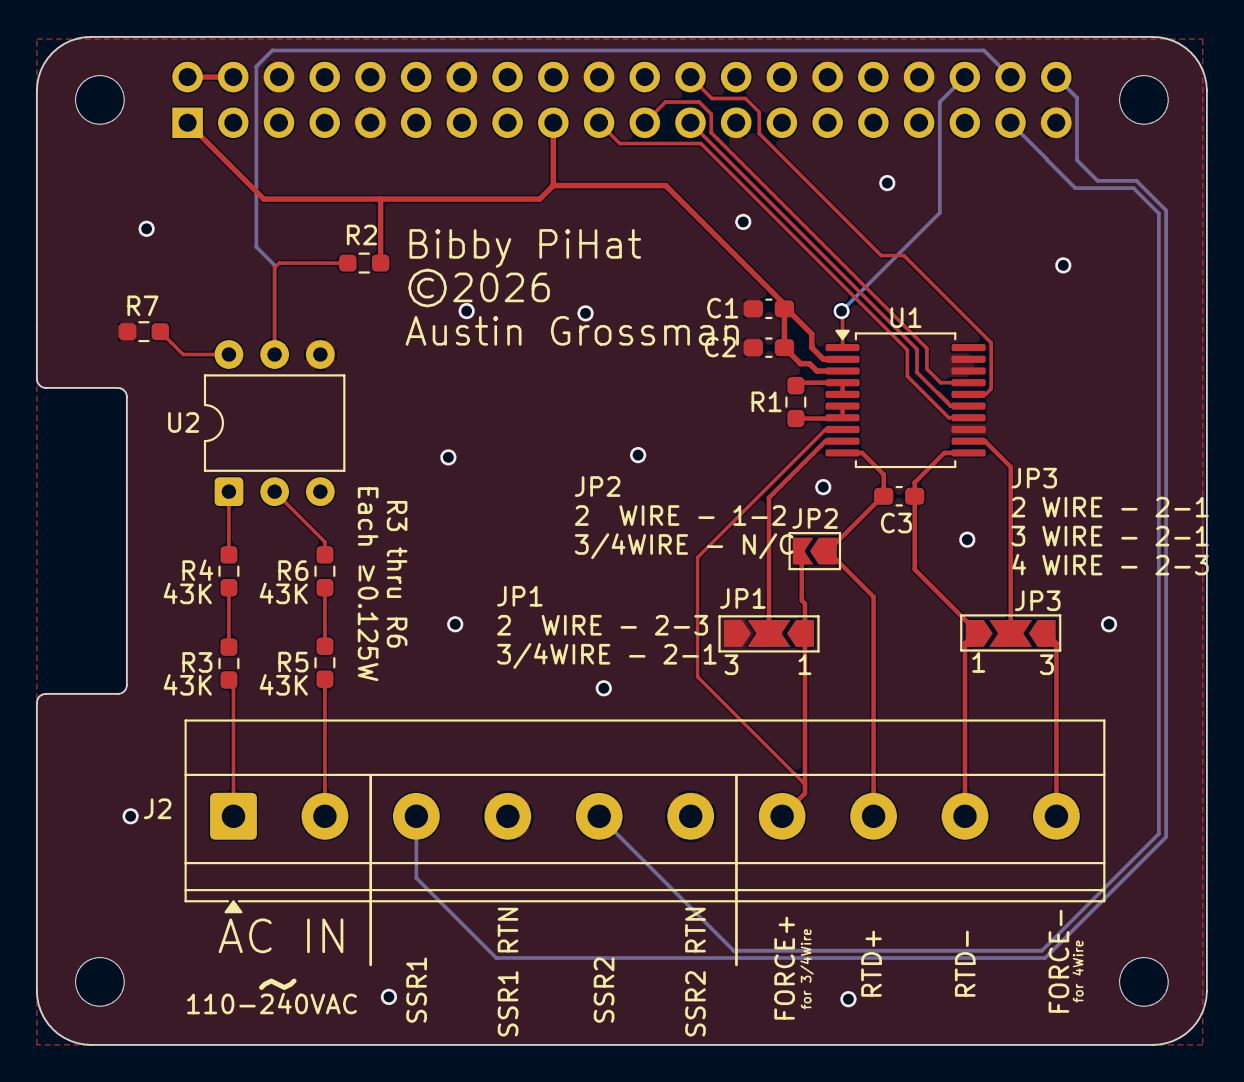
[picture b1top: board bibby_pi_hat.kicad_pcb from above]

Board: 2 copper layers, 65.0 x 56.0 mm, 21 parts (1 on the bottom side), 26 nets.

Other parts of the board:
MH1, MH2, MH3, MH4: MountingHole_2.7mm_M2.5

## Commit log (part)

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2026-04-25 First hash out of architecture. Worked on heater-controller and should be mostly done. Not built or tested yet.
2026-04-25 frontend bare bones; compiles and runs. no input working. backend seems to work; needs more rigorous testing
2026-04-27 heater-controller working so far. need to test zero cross input. frontend inputs working.
2026-06-17 Still need to test the zero cross input. Temp sensing works and has been tested and passes through a second order moving average filter some restructuring of the display to make it work better. Signa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
2026-06-17 added raspberry pi hat for temp sensor chip, zero crossing detector, and output to SSRs.
2026-06-17 corrections on pi_hat. DRDYn from max chip went to wrong pin and two grounds of max chip weren't connected.
2026-06-17 Timeout for zerocrossing watchdig now a #define. heater-controller and frontend both ensure that only one instance of each can run at a given time. The shared memory between the two processes are nev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
2026-06-19 Rehaul of GUI
2026-06-19 INI config system, CSV logging, PID completion, Apache-2.0 license, comprehensive README
    - shared/config.{h,c} + bibby.ini: INI loader for mains frequency, element
    wattage/area, and PID gains; both processes load at startup
    - frontend/csv_logger.{h,cpp}: per-run timestamped CSV with PID terms, temp,
    duty, fault state; flushed each row for crash safety
    - PID: PidTerms struct for logging/tuning; kp/ki/kd wired from config
    - MAX31865: mains filter notch (50/60 Hz) driven from config
2026-06-24 Holding feedforward, conditional-integration anti-windup, decoupled sampling, plant-ID tooling
    PID/control:
    - PidController::update() takes a feedforward arg; output is clamp(ff + p + i + d).
    New [feedforward] INI section (process_gain_c, ambient_c) sized from the step
    test; process_gain_c = 0 disables it (safe default). Feedforward depends on the
    setpoint, not the measurement, so it does not affect loop stability.
    - Replace unconditional integration with conditional integration: hold the

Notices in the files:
README.md:
12. License:
bibby uses three licenses, one per artifact type:
Artifact | License | File
Software (`src/`, `tests/`, `tools/`, `deploy/`) | Apache-2.0 | [`LICENSE`](LICENSE)
Hardware (`pi_hat/`) | CERN-OHL-P-2.0 | [`pi_hat/LICENSE`](pi_hat/LICENSE)
Documentation (`README.md`, `docs/`) | CC-BY-4.0 | [creativecommons.org/licenses/by/4.0](https://creativecommons.org/licenses/by/4.0/)
Apache-2.0** (software): permissive, includes an explicit patent grant so
techniques in the control code cannot be used against you or downstream users.
No per-file headers are required; the to
